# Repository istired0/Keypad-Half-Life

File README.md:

# Keypad

Previously known as: Really-good-keyboard

This is a keypad (& keyboard) made for the Half-life event by Hack-Club

# Features 
- 2x Knobs                                                                                                                                                                        
- 10x customizable keys
- KMK firmware

# Enclosure
No screws needed! The snap design allows easy and fast access in case something goes wrong (hopefully  nothing)

Print settings:
- Material: PLA
- Infill: 20%
- Color: Black
- Layer Height: 0.2mm

# BOM 

| Item Name | Qty | Price (total) (USD) | Item link | Notes |
|---|---:|---:|---|---|
| PCB | 1 | $4.00 | [Link](https://github.com/istired0/Really-good-keyboard/blob/main/KeyBad.zip) | |
| Switches | 1 | $4.91 | [Link](https://www.aliexpress.com/item/1005009607951741.html?mp=1) | |
| Keycaps | 10 | $2.10 | [Link](https://www.aliexpress.com/item/1005009795511586.html?mp=1&pdp_ext_f=%7B%22cart2PdpParams%22%3A%7B%22pdpBusinessMode%22%3A%22retail%22%7D%7D) | |
| Special keycap | 1 | $0.34 | [Link](https://www.aliexpress.com/item/1005009795511586.html?mp=1&pdp_ext_f=%7B%22cart2PdpParams%22%3A%7B%22pdpBusinessMode%22%3A%22retail%22%7D%7D) | |
| Rotary Encoder | 3 | $1.86 | [Link](https://www.aliexpress.com/item/1005008773438800.html?mp=1) | |
| Encoder Cap | 1 | $1.57 | [Link](https://www.aliexpress.com/item/1005006046615939.html?mp=1&pdp_ext_f=%7B%22cart2PdpParams%22%3A%7B%22pdpBusinessMode%22%3A%22retail%22%7D%7D) | |
| Diodes | 1 | $1.10 | [Link](https://www.aliexpress.com/item/1005003394917074.html?mp=1) | |
| Seeed Xiao RP2040 | 1 | $4.90 | [Link](https://www.seeedstudio.com/Seeed-Studio-XIAO-RP2040-Pre-Soldered-p-6333.html) | |
| Pins | 1 | $0.50 | [Link](https://www.aliexpress.com/item/4001198421663.html?algo_exp_id=00f90cdb-f918-42e6-a130-e38f20f6ef74-9&pdp_ext_f=%7B%22order%22%3A%2221710%22%2C%22spu_best_type%22%3A%22price%22%2C%22eval%22%3A%22price%22%2C%22fromPage%22%3A%22search%22%7D&utparam-url=scene%3Asearch%7Cquery_from%3A%7Cx_object_id%3A4001198421663%7C_p_origin_prod%3A) | |
| Tax & Shipping | | $39.27 | | |
| **Total Price (USD)** | | **$60.55** | | |

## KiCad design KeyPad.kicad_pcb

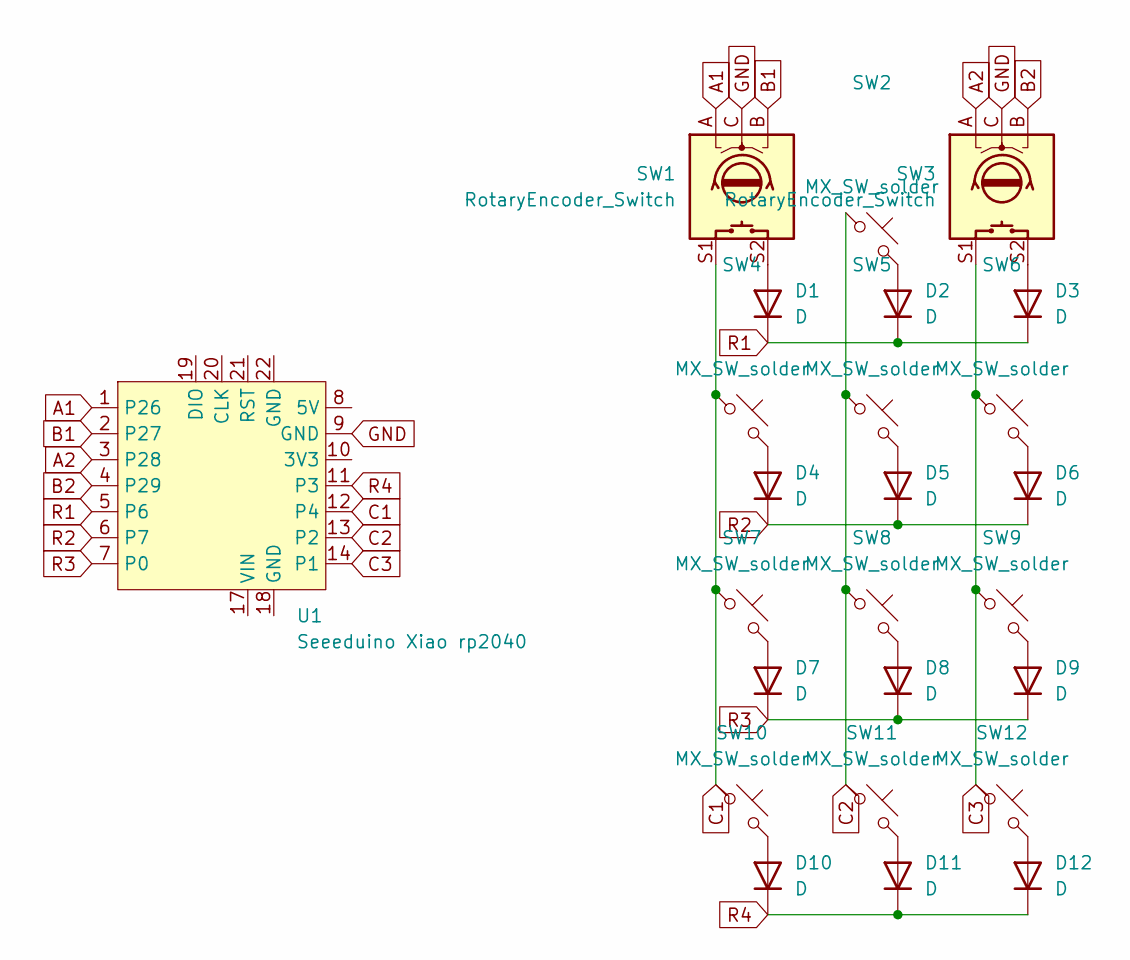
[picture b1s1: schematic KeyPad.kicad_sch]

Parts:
D1, D2, D3, D4, D5, D6, D7, D8, D9, D10, D11, D12: D; D_SOD-123
SW1, SW3: RotaryEncoder_Switch; ROT_Alps_EC11E-Switch
SW2, SW4, SW5, SW6, SW7, SW8, SW9, SW10, SW11, SW12: MX_SW_solder; SW_MX_1u
U1: Seeeduino Xiao rp2040; Xiao_rp2040_ACH

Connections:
A1: SW1.A, U1.1 (P26)
A2: SW3.A, U1.3 (P28)
B1: SW1.B, U1.2 (P27)
B2: SW3.B, U1.4 (P29)
C1: SW1.S1, SW4.1, SW7.1, SW10.1, U1.12 (P4)
C2: SW2.1, SW5.1, SW8.1, SW11.1, U1.13 (P2)
C3: SW3.S1, SW6.1, SW9.1, SW12.1, U1.14 (P1)
GND: SW1.C, SW3.C, U1.9 (GND)
unnamed: D1.2 (A), SW1.S2
unnamed: D2.2 (A), SW2.2
unnamed: D3.2 (A), SW3.S2
unnamed: D4.2 (A), SW4.2
unnamed: D5.2 (A), SW5.2
unnamed: D6.2 (A), SW6.2
unnamed: D7.2 (A), SW7.2
unnamed: D8.2 (A), SW8.2
unnamed: D9.2 (A), SW9.2
unnamed: D10.2 (A), SW10.2
unnamed: D11.2 (A), SW11.2
unnamed: D12.2 (A), SW12.2
R1: D1.1 (K), D2.1 (K), D3.1 (K), U1.5 (P6)
R2: D4.1 (K), D5.1 (K), D6.1 (K), U1.6 (P7)
R3: D7.1 (K), D8.1 (K), D9.1 (K), U1.7 (P0)
R4: D10.1 (K), D11.1 (K), D12.1 (K), U1.11 (P3)

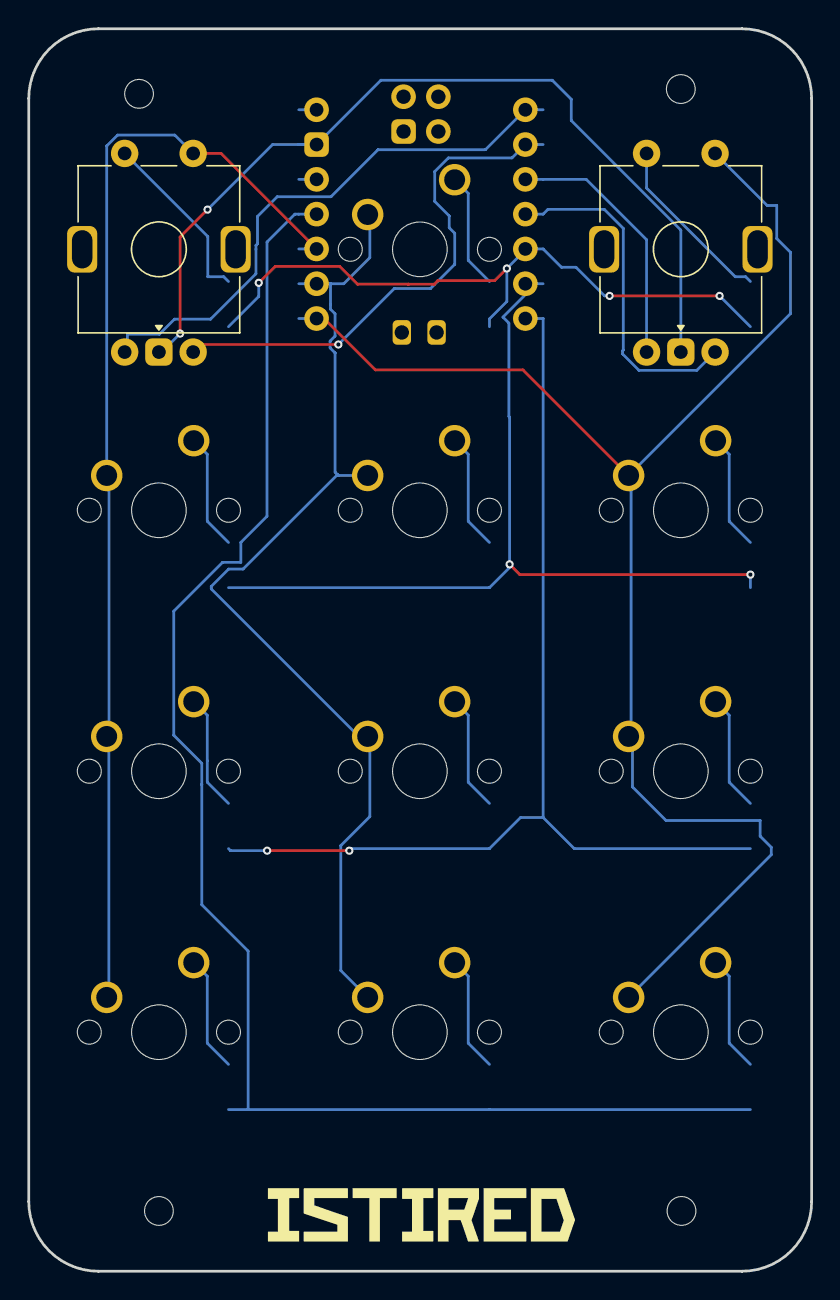
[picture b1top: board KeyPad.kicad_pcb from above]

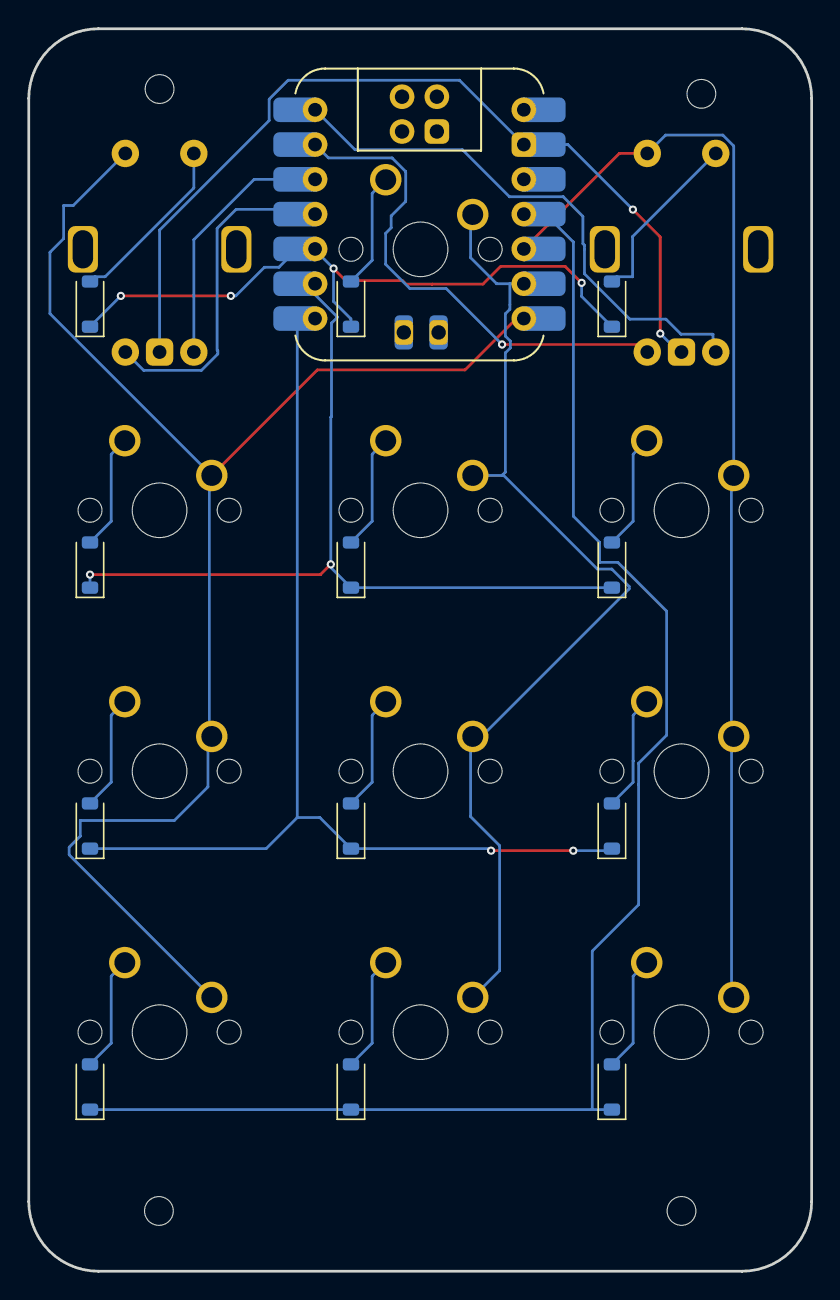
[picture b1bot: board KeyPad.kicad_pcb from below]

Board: 2 copper layers, 57.1 x 90.7 mm, 25 parts (13 on the bottom side), 24 nets.

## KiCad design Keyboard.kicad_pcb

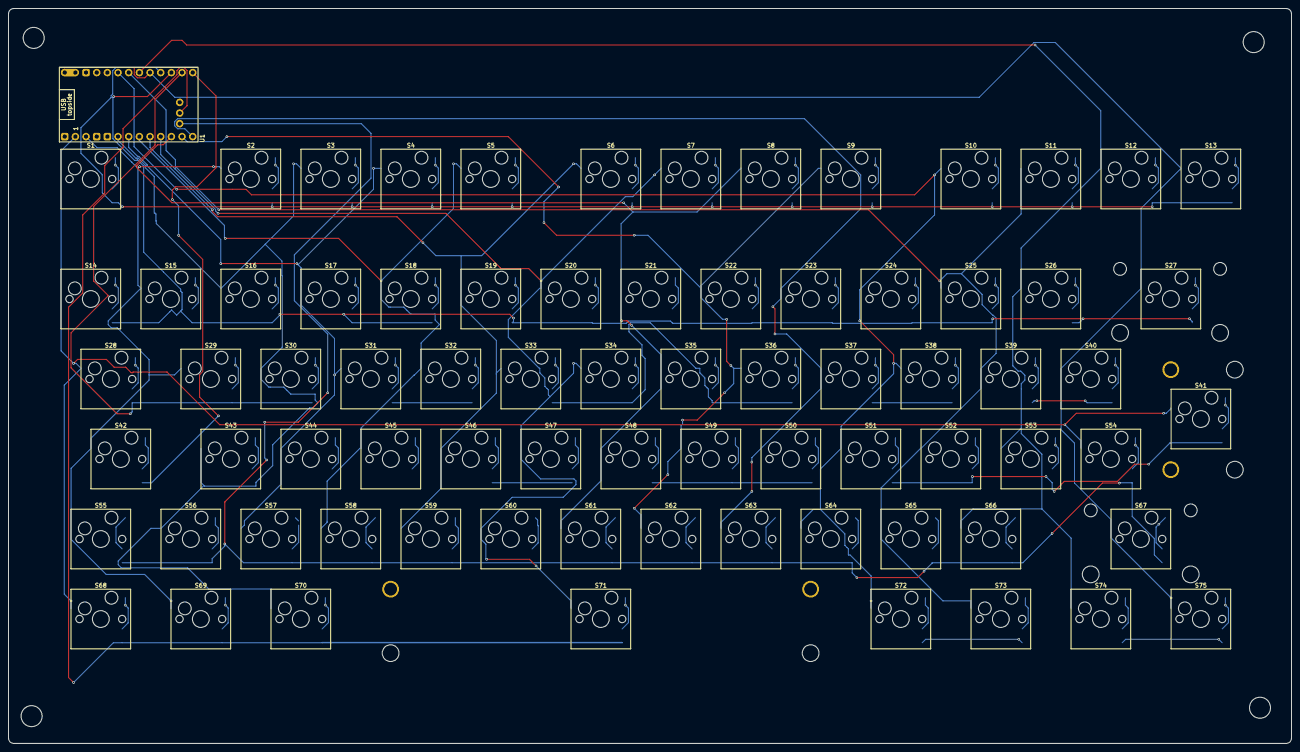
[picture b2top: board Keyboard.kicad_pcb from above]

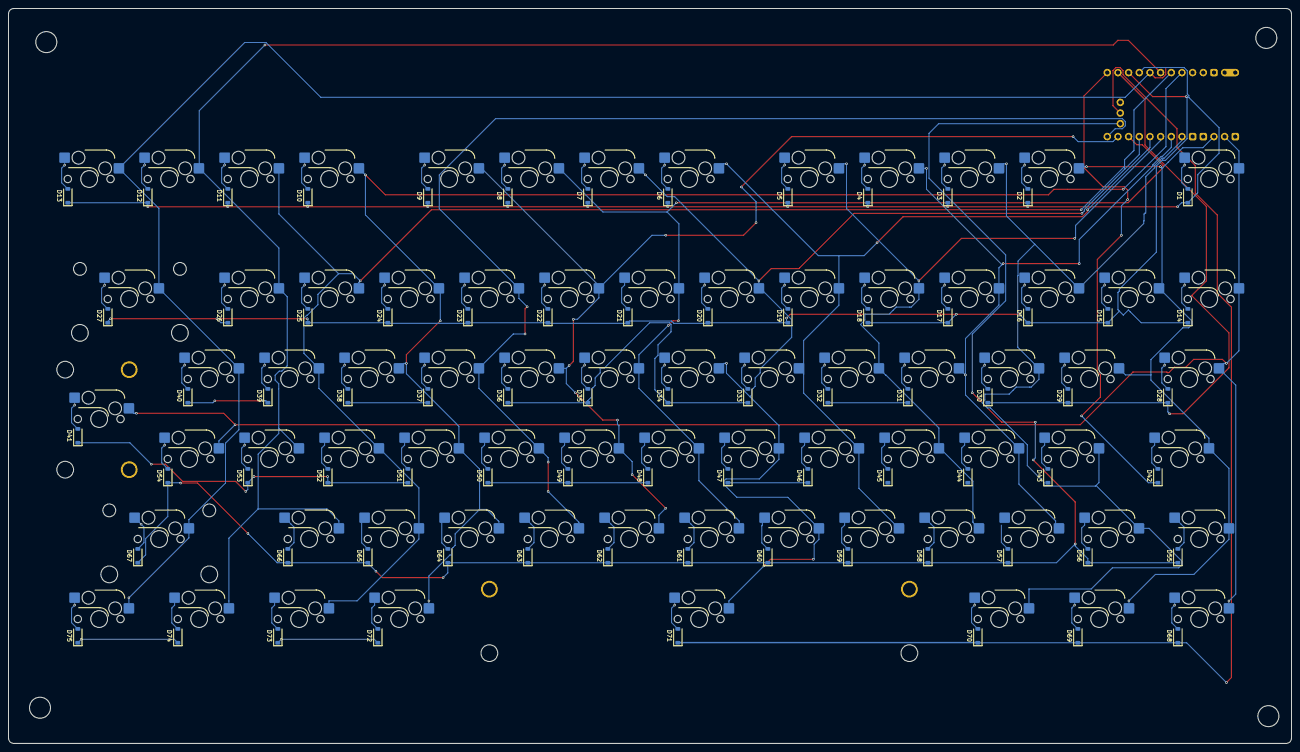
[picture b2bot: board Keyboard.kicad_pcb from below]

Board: 2 copper layers, 305.5 x 175.0 mm, 159 parts (75 on the bottom side), 97 nets.

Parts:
D1, D2, D3, D4, D5, D6, D7, D8, D9, D10, D11, D12, D13, D14, D15, D16, D17, D18, D19, D20, D21, D22, D23, D24, D25, D26, D27, D28, D29, D30, D31, D32, D33, D34, D35, D36, D37, D38, D39, D40, D41, D42, D43, D44, D45, D46, D47, D48, D49, D50, D51, D52, D53, D54, D55, D56, D57, D58, D59, D60, D61, D62, D63, D64, D65, D66, D67, D68, D69, D70, D71, D72, D73, D74, D75: D_SOD-123
H1, H2, H3, H4: MountingHole; MountingHole_5mm
S1, S2, S3, S4, S5, S6, S7, S8, S9, S10, S11, S12, S13, S14, S15, S16, S17, S18, S19, S20, S21, S22, S23, S24, S25, S26, S27, S28, S29, S30, S31, S32, S33, S34, S35, S36, S37, S38, S39, S40, S41, S42, S43, S44, S45, S46, S47, S48, S49, S50, S51, S52, S53, S54, S55, S56, S57, S58, S59, S60, S61, S62, S63, S64, S65, S66, S67, S68, S69, S70, S71, S72, S73, S74, S75: Istired
T1: MX_MX1tab; STAB_MX_P_ISO
T2: MX_MX1tab; STAB_MX_P_6.25u
T3: MX_MX1tab; STAB_MX_2u
T4: MX_MX1tab; STAB_MX_2.75u
U1: uperMini nRF52840; SuperMini_nRF52840_AH_USBup

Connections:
C1: S1.1, S14.1, S28.1, S41.1, S54.1, S68.1, U1.1 (P0.06)
C2: S2.1, S15.1, S29.1, S42.1, S55.1, S69.1, U1.2 (P0.08)
C3: S3.1, S16.1, S30.1, S43.1, S56.1, S70.1, U1.5 (P0.17)
C4: S4.1, S17.1, S31.1, S44.1, S57.1, U1.6 (P0.20)
C5: S5.1, S18.1, S32.1, S45.1, S58.1, U1.7 (P0.22)
C6: S6.1, S19.1, S33.1, S46.1, S59.1, U1.8 (P0.24)
C7: S7.1, S20.1, S34.1, S47.1, S60.1, S71.1, U1.9 (P1.00)
C8: S8.1, S21.1, S35.1, S48.1, S61.1, U1.10 (P0.11)
C9: S9.1, S22.1, S36.1, S49.1, S62.1, U1.11 (P1.04-LF)
C10: S23.1, S37.1, S50.1, S63.1, U1.12 (P1.06-LF)
C11: S10.1, S24.1, S38.1, S51.1, S64.1, S72.1, U1.17 (P0.31-LF)
C12: S11.1, S25.1, S39.1, S52.1, S65.1, S73.1, U1.18 (P0.29-LF)
C13: S12.1, S26.1, S53.1, S66.1, S74.1, U1.19 (P0.02-LF)
C14: S13.1, S27.1, S40.1, S67.1, S75.1, U1.20 (P1.15-LF)
unnamed: D1.2 (A), S1.2
unnamed: D2.2 (A), S2.2
unnamed: D3.2 (A), S3.2
unnamed: D4.2 (A), S4.2
unnamed: D5.2 (A), S5.2
unnamed: D6.2 (A), S6.2
unnamed: D7.2 (A), S7.2
unnamed: D8.2 (A), S8.2
unnamed: D9.2 (A), S9.2
unnamed: D10.2 (A), S10.2
unnamed: D11.2 (A), S11.2
unnamed: D12.2 (A), S12.2
unnamed: D13.2 (A), S13.2
unnamed: D14.2 (A), S14.2
unnamed: D15.2 (A), S15.2
unnamed: D16.2 (A), S16.2
unnamed: D17.2 (A), S17.2
unnamed: D18.2 (A), S18.2
unnamed: D19.2 (A), S19.2
unnamed: D20.2 (A), S20.2
unnamed: D21.2 (A), S21.2
unnamed: D22.2 (A), S22.2
unnamed: D23.2 (A), S23.2
unnamed: D24.2 (A), S24.2
unnamed: D25.2 (A), S25.2
unnamed: D26.2 (A), S26.2
unnamed: D27.2 (A), S27.2
unnamed: D28.2 (A), S28.2
unnamed: D29.2 (A), S29.2
unnamed: D30.2 (A), S30.2
unnamed: D31.2 (A), S31.2
unnamed: D32.2 (A), S32.2
unnamed: D33.2 (A), S33.2
unnamed: D34.2 (A), S34.2
unnamed: D35.2 (A), S35.2
unnamed: D36.2 (A), S36.2
unnamed: D37.2 (A), S37.2
unnamed: D38.2 (A), S38.2
unnamed: D39.2 (A), S39.2
unnamed: D40.2 (A), S40.2
unnamed: D41.2 (A), S41.2
unnamed: D42.2 (A), S42.2
unnamed: D43.2 (A), S43.2
unnamed: D44.2 (A), S44.2
unnamed: D45.2 (A), S45.2
unnamed: D46.2 (A), S46.2
unnamed: D47.2 (A), S47.2
unnamed: D48.2 (A), S48.2
unnamed: D49.2 (A), S49.2
unnamed: D50.2 (A), S50.2
unnamed: D51.2 (A), S51.2
unnamed: D52.2 (A), S52.2
unnamed: D53.2 (A), S53.2
unnamed: D54.2 (A), S54.2
unnamed: D55.2 (A), S55.2
unnamed: D56.2 (A), S56.2
unnamed: D57.2 (A), S57.2
unnamed: D58.2 (A), S58.2
unnamed: D59.2 (A), S59.2
unnamed: D60.2 (A), S60.2
unnamed: D61.2 (A), S61.2
unnamed: D62.2 (A), S62.2
unnamed: D63.2 (A), S63.2
unnamed: D64.2 (A), S64.2
unnamed: D65.2 (A), S65.2
unnamed: D66.2 (A), S66.2
unnamed: D67.2 (A), S67.2
unnamed: D68.2 (A), S68.2
unnamed: D69.2 (A), S69.2
unnamed: D70.2 (A), S70.2
unnamed: D71.2 (A), S71.2
unnamed: D72.2 (A), S72.2
unnamed: D72.1 (K), D73.1 (K)
unnamed: D73.2 (A), S73.2
unnamed: D74.2 (A), S74.2
unnamed: D74.1 (K), D75.1 (K)
unnamed: D75.2 (A), S75.2
R1: D1.1 (K), D2.1 (K), D3.1 (K), D4.1 (K), D5.1 (K), D6.1 (K), D7.1 (K), D8.1 (K), D9.1 (K), D10.1 (K), D11.1 (K), D12.1 (K), D13.1 (K), U1.21 (P1.13-LF)
R2: D14.1 (K), D15.1 (K), D16.1 (K), D17.1 (K), D18.1 (K), D19.1 (K), D20.1 (K), D21.1 (K), D22.1 (K), D23.1 (K), D24.1 (K), D25.1 (K), D26.1 (K), D27.1 (K), U1.22 (P1.11-LF)
R3: D28.1 (K), D29.1 (K), D30.1 (K), D31.1 (K), D32.1 (K), D33.1 (K), D34.1 (K), D35.1 (K), D36.1 (K), D37.1 (K), D38.1 (K), D39.1 (K), D40.1 (K), U1.23 (P0.10-LF)
R4: D41.1 (K), D42.1 (K), D43.1 (K), D44.1 (K), D45.1 (K), D46.1 (K), D47.1 (K), D48.1 (K), D49.1 (K), D50.1 (K), D51.1 (K), D52.1 (K), D53.1 (K), U1.24 (P0.09-LF)
R5: D54.1 (K), D55.1 (K), D56.1 (K), D57.1 (K), D58.1 (K), D59.1 (K), D60.1 (K), D61.1 (K), D62.1 (K), D63.1 (K), D64.1 (K), D65.1 (K), D66.1 (K), D67.1 (K), U1.25 (P1.01-LF)
R6: D68.1 (K), D69.1 (K), D70.1 (K), D71.1 (K), U1.26 (P1.02-LF)
